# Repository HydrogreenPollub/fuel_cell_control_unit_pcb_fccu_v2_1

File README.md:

# fuel_cell_control_unit_pcb_fccu_v2_1

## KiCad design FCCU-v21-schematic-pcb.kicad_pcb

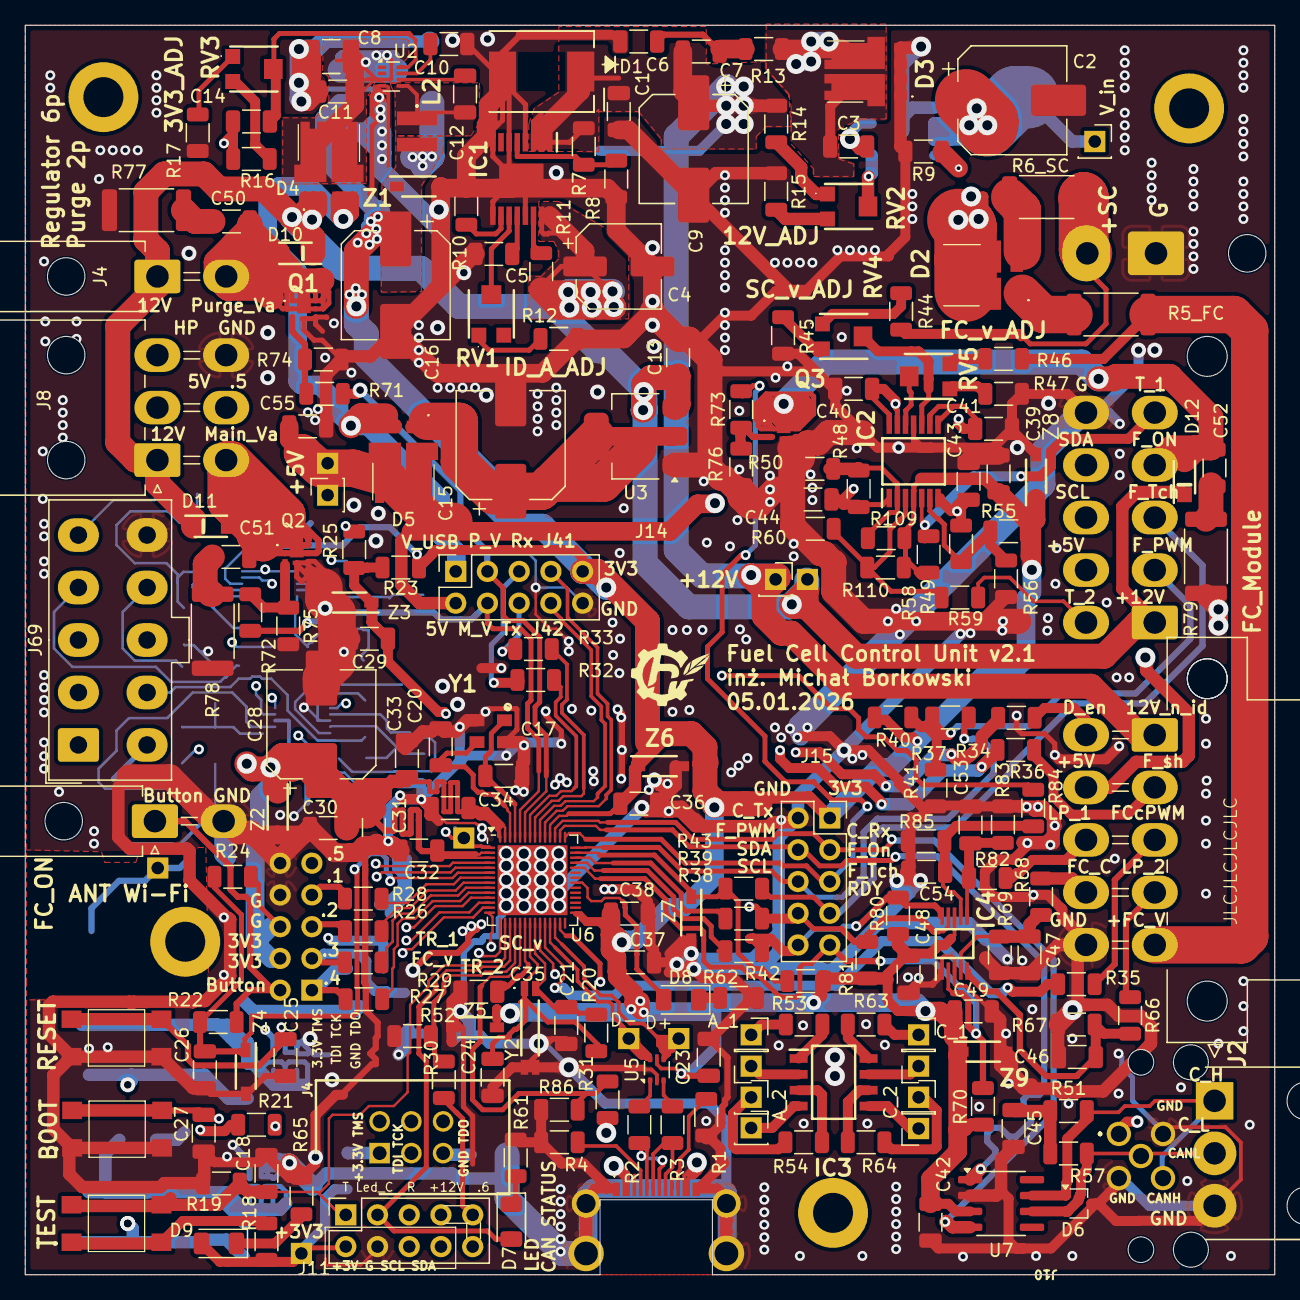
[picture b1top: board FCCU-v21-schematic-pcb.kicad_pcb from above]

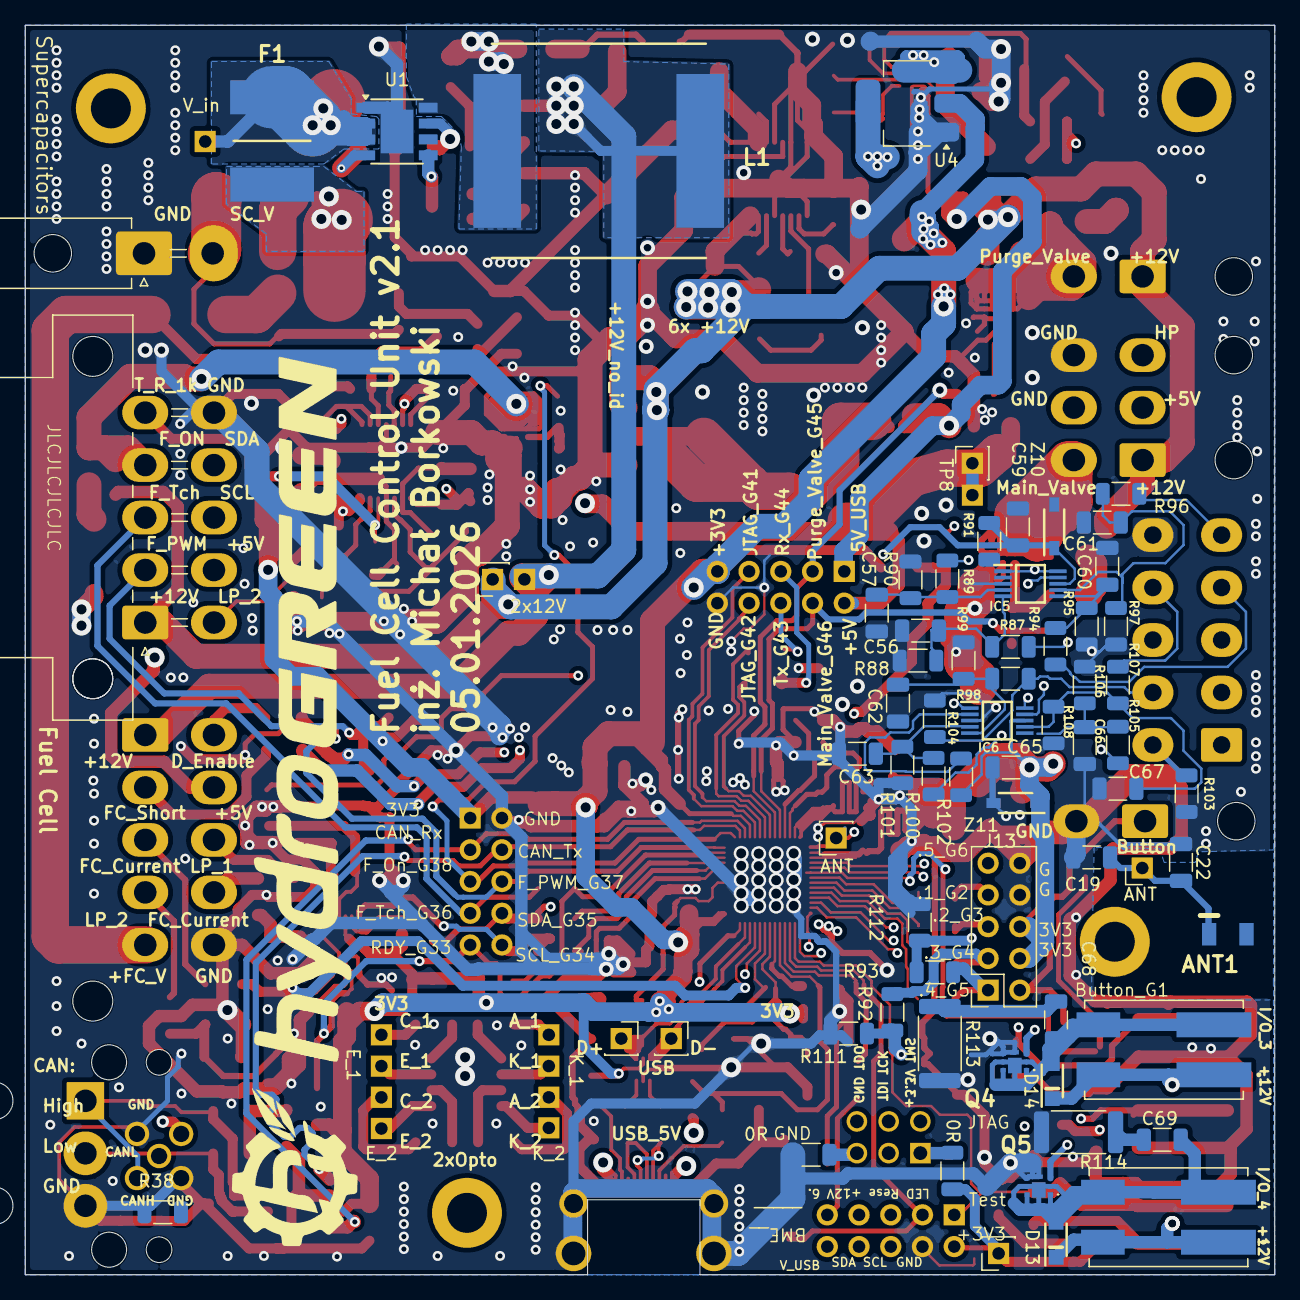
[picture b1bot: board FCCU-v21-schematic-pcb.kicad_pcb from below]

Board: 4 copper layers, 100.0 x 100.0 mm, 276 parts (68 on the bottom side), 165 nets.

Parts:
0R, 0R#2: 0; R_1206_3216Metric
2x12V: +5V; PinSocket_1x01_P2.54mm_Vertical
+3V3: +3.3V; PinSocket_1x01_P2.54mm_Vertical
+5V, +12V: +5V; PinSocket_1x01_P2.54mm_Vertical
ANT: Ant; PinSocket_1x01_P2.54mm_Vertical
ANT1: 2450AT18B100E; ANTC3216X140N
A_1: A_1; PinSocket_1x01_P2.54mm_Vertical
A_2: A_2; PinSocket_1x01_P2.54mm_Vertical
BOOT: TL3305BF100QG; TL3305BF160QG
C1, C13, C30, C33, C38, C55: 1u; C_1206_3216Metric
C2: 10u 100V; CP_Elec_8x10.5
C3: 2n2 100V; C_1206_3216Metric
C4: 47u; CP_Elec_6.3x7.7
C5: 2n7; C_1206_3216Metric
C6, C14: 47p; C_1206_3216Metric
C7: 3n3; C_1206_3216Metric
C8: 1-10u; C_1210_3225Metric_Pad1.33x2.70mm_HandSolder
C9, C15: 22u; CP_Elec_8x10.5
C10: 33n; C_1206_3216Metric
C11, C12, C18, C23, C25, C27, C31, C32, C35, C36, C37, C39, C42, C48: 100n; C_1206_3216Metric
C16: 100u; CP_Elec_8x10.5
C17, C20: 12p; C_1206_3216Metric
C19, C22: 1p2; C_1206_3216Metric
C21, C24: 20p; C_1206_3216Metric
C26, C29: 0; C_1206_3216Metric
C28: 10u; CP_Elec_8x10.5
C34: 10n; C_1206_3216Metric
C40, C41, C44, C46, C47, C53, C54: c; C_1206_3216Metric
C43, C45: 4n7; C_1206_3216Metric
C49, C59, C65: 4N7; C_1206_3216Metric
C50, C51, C52, C68, C69: 20n; C_1206_3216Metric
C56, C57, C60, C61, C66, C67: NP; C_1206_3216Metric
C62, C63: 3n; C_1206_3216Metric
C_1: C_1; PinSocket_1x01_P2.54mm_Vertical
C_2: C_2; PinSocket_1x01_P2.54mm_Vertical
D1: TPSMC30CA; TPSMCSeries_LTF
D2, D3, D4, D5: V10K100DUHM3_H; V10K100DUHM3H
D6: SP0502BAJT; SOT-323_SC-70
D7, D8, D9: LED; LED_1206_3216Metric
D10, D11, D12, D13, D14: PMEG10020; PMEG10020ELR
E_1: E_1; PinSocket_1x01_P2.54mm_Vertical
E_2: E_2; PinSocket_1x01_P2.54mm_Vertical
F1: 3A; FUSC8664X180N
I/O_3  +12V, I/O_4  +12V: 2060-453/998-404; WAGO-2060-452-998-404
IC1: LM76202QPWPRQ1; SOP65P640X120-17N
IC2: AD8544ARUZ-REEL; SOP65P640X120-14N
IC3: ILD206T; SOIC127P610X323-8N
IC4, IC5, IC6: ADS1015IDGSR; SOP50P490X110-10N
J1: Supercapacitors; Molex_Mini-Fit_Jr_5569-02A2_2x01_P4.20mm_Horizontal
J2: CAN; 39303035
J4: P_Valve; Molex_Mini-Fit_Jr_5569-02A2_2x01_P4.20mm_Horizontal
J4#2: 61200621621
J5: FC_ON; Molex_Mini-Fit_Jr_5569-02A2_2x01_P4.20mm_Horizontal
J6: FC Module; Molex_Mini-Fit_Jr_5569-10A1_2x05_P4.20mm_Horizontal
J7: FC Cooling; Molex_Mini-Fit_Jr_5569-10A1_2x05_P4.20mm_Horizontal
J8: M_Valve; Molex_Mini-Fit_Jr_5569-06A2_2x03_P4.20mm_Horizontal
J10: M12A-05PMMR-SF7003; M12A05PMMRSF7003
J11: BME; PinSocket_2x05_P2.54mm_Vertical
J13: I/O; PinSocket_2x05_P2.54mm_Vertical
J14: Top signals; PinSocket_2x05_P2.54mm_Vertical
J15: Fuel cell signals; PinSocket_2x05_P2.54mm_Vertical
J69: ADC, Freq, 4-20mA; Molex_Mini-Fit_Jr_5566-10A_2x05_P4.20mm_Vertical
K_1: K_1; PinSocket_1x01_P2.54mm_Vertical
K_2: K_2; PinSocket_1x01_P2.54mm_Vertical
L1: IHLP6767DZER470M11
L2: 4u7; SRN3015TA4R7M
P1: USB_C_Plug_USB2.0; 2169900002
Q1, Q2, Q3, Q4, Q5: PMPB10XNX; PMPB15XPAX
R1, R4: 5k1; R_1206_3216Metric
R2, R3, R72, R73: 0; R_1206_3216Metric
R5_FC, R6_SC: 0R; R_2512_6332Metric
R7: 180k; R_1206_3216Metric
R8, R87, R89, R94, R96: 12k; R_1206_3216Metric
R9, R10, R11: 100k; R_1206_3216Metric
R12: 5k6; R_1206_3216Metric
R13: 143k; R_1206_3216Metric
R14: 453k; R_1206_3216Metric
R15: 49k9; R_1206_3216Metric
R16: 47k; R_1206_3216Metric
R17, R67, R69, R83, R85, R86, R106, R108: 15k; R_1206_3216Metric
R18, R19, R21, R23, R24, R31, R40, R41, R42, R48, R49, R52, R55, R58, R66, R68, R74, R75, R76, R82, R84, R105, R107, R109, R110, R111, R112: 10k; R_1206_3216Metric
R20: 5M; R_1206_3216Metric
R22, R25, R26, R28, R30, R34, R35, R36, R43, R50, R53, R54, R56, R61, R62, R63, R64, R65: 1k; R_1206_3216Metric
R27, R29, R37: 200R; R_1206_3216Metric
R32, R33: 100R; R_1206_3216Metric
R38, R38#2, R39, R59: 0R; R_1206_3216Metric
R44, R46: 6k8; R_1206_3216Metric
R45, R47: 3k3; R_1206_3216Metric
R51, R57: 60; R_1206_3216Metric
R60: k; R_1206_3216Metric
R70, R91, R102: 2k; R_1206_3216Metric
R71: 180R; R_1206_3216Metric
R77, R78, R79, R113, R114: 100R 0,5W; R_2512_6332Metric
R80, R81: 4k7; R_1206_3216Metric
R88, R90, R95, R97: 18k; R_1206_3216Metric
R92, R93: 20; R_1206_3216Metric
R98, R100: 6k; R_1206_3216Metric
R99, R101: 130k; R_1206_3216Metric
R103, R104: 150R; R_1206_3216Metric
RESET: TL3305BF100QG; TL3305BF160QG
RV1, RV2: Pot_12V 20k; TC33X2503E
RV3: Pot_12V 5k; TC33X2503E
RV4, RV5: Pot_12V 2k; TC33X2503E
TEST: TL3305BF100QG; TL3305BF160QG
TP3: Ant; PinSocket_1x01_P2.54mm_Vertical
TP8: +5V; PinSocket_1x01_P2.54mm_Vertical
TP12: USB_D+; PinSocket_1x01_P2.54mm_Vertical
TP13: USB_D-; PinSocket_1x01_P2.54mm_Vertical
U1: LM5013DDAR; Diodes_SO-8EP
U2: TPS62933; SOT-583-8
U3: LDI1117-05H; SOT-223-3_TabPin2
U4: LDI1117-3.3H; SOT-223-3_TabPin2
U5: USBLC6-2P6; SOT-666
U6: ESP32-S3FN8; QFN-56-1EP_7x7mm_P0.4mm_EP5.6x5.6mm
U7: SN65HVD232; SOIC-8_3.9x4.9mm_P1.27mm
V_in: Vin test; PinSocket_1x01_P2.54mm_Vertical
Y1: Crystal_40MHz; KC3225K400000C1GE00
Y2: 9HT7-32.768KDZF-T; 9HT732768KDZFT
Z1, Z2, Z3, Z4, Z5, Z6, Z7, Z8, Z9, Z10, Z11: MMSZ3V3T1G; SOD3716X135N

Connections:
+3.3V: 0R.2, +3V3.1, C14.1, C16.1, C23.1, C28.1, C30.1, C31.1, C32.1, C33.1, C34.1, C35.1, C36.1, C37.1, C38.1, C39.1, C42.1, C48.1, C49.1, C59.1, C65.1, D9.2 (A), IC2.4 (V+), IC4.8 (VDD), IC5.8 (VDD), IC6.1 (ADDR), IC6.8 (VDD), J11.6, J13.7, J13.8, J14.5, J15.1, L2.2, R16.1, R18.2, R21.2, R23.2, R24.2, R40.2, R42.2, R55.1, R58.1, R70.1, R80.1, R81.1, R91.1, R102.1, R109.2, R110.1, U4.2 (VO), U5.5 (VBUS), U6.2 (VDD3P3), U6.3 (VDD3P3), U6.20 (VDD3P3_RTC), U6.29 (VDD_SPI), U6.46 (VDD3P3_CPU), U6.55 (VDDA), U6.56 (VDDA), U7.3 (VCC), Z1.1 (K), Z2.1 (K), Z5.1 (K), Z6.1 (K), Z8.1 (K), Z9.1 (K), Z10.1 (K), Z11.1 (K)
+3V3: 0R.1, J4#2.1
+5V: +5V.1, C55.1, D5.5, D5.6, D5.7, D5.8, J6.7, J7.7, J8.2, J14.6, TP8.1 (1_1)
+12V: 2x12V.1, +12V.1, C4.1, C13.1, D4.1, D4.2, D10.1 (K), D11.1 (K), D12.1 (K), D13.1 (K), D14.1 (K), IC1.15 (OUT_1), IC1.16 (OUT_2), J4.1, J7.1, J8.1, J11.4, J69.1, R11.1, U3.3 (VI)
/12V_no_id: C1.1, C7.2, C9.1, D1.2 (A), IC1.1 (IN_1), IC1.2 (IN_2), IC1.3 (UVLO), J6.1, J10.1, L1.2, R7.1, R14.2
/IO2/ADC2_0: J69.2, R89.1
/IO2/ADC2_1: J69.3, R87.1
/IO2/ADC2_2: J69.4, R94.1
/IO2/ADC2_3: J69.5, R96.1
/IO2/ADC3_0: J69.6, R100.1, R103.1
/IO2/ADC3_1: J69.7, R98.1, R104.1
/IO2/ADC3_2: J69.8, R105.1
/IO2/ADC3_3: J69.9, R107.1
/IO2/I/O_3: C68.1, D14.2 (A), Q4.1 (D)
/IO2/I/O_4: C69.1, D13.2 (A), Q5.1 (D)
/IO2/SCL_MCU: IC5.1 (ADDR), IC5.10 (SCL), IC6.10 (SCL)
/IO2/SDA_MCU: IC5.9 (SDA), IC6.9 (SDA)
/IO/CANH: D6.1 (K), J2.1, J10.3, R51.2, U7.7 (CANH)
/IO/CANL: D6.2 (K), J2.2, J10.5, R57.2, U7.6 (CANL)
/IO/CAN_RX_G39: J4#2.TDO, U7.4 (R)
/IO/FAN_ON: C52.1, D12.2 (A), J7.4, Q3.1 (D)
/IO/FAN_ON_MCU: J15.3, R73.2
/IO/FAN_TACHO: J7.3, J15.4
/IO/FC_C: J6.9, R68.1
/IO/FC_V: J6.5, R5_FC.1, R46.2
/IO/FC_VOLTAGE_MCU: C40.2, IC2.13 (-IN_D), IC2.14 (OUT_D)
/IO/HP: J8.3, R84.1
/IO/LED_CAN_STATUS: D7.2 (A), J11.2
/IO/LP_1: J6.8, R82.1
/IO/LP_2: J6.4, R66.1
/IO/MAIN_VALVE_MCU: J14.7, R72.2
/IO/Main_Valve: C51.1, D11.2 (A), J8.4, Q2.1 (D)
/IO/PURGE_VALVE: C50.1, D10.2 (A), J4.2, Q1.1 (D)
/IO/PURGE_VALVE_MCU: J14.2, R71.2
/IO/RDY_MCU: IC4.2 (ALERT/RDY), J15.5, R70.2
/IO/SCL_FC: IC4.10 (SCL), J7.8, J15.10, R80.2
/IO/SC_V: J1.2, R6_SC.1, R44.2
/IO/SC_VOLTAGE_MCU: C41.2, IC2.8 (OUT_C), IC2.9 (-IN_C)
/IO/SDA_FC: IC4.9 (SDA), J7.9, J15.9, R81.2
/IO/T1_G10: C43.1, IC2.7 (OUT_B), R49.2
/IO/T2_G7: C44.2, IC2.1 (OUT_A), R48.1
/IO/TEMP_SENSOR_1: IC2.5 (+IN_B), J7.5, R58.2
/IO/TEMP_SENSOR_2: IC2.3 (+IN_A), J7.6, R59.1
/MCU/Antena: ANT.1, C22.1, TP3.1 (1_1), U6.1 (LNA_IN/RF)
/MCU/BOOT: BOOT.3 (K), BOOT.4 (A), C27.1, U6.5 (GPIO0/BOOT)
/MCU/BUTTON_MCU_G36: J5.1, J13.6
/MCU/FAN_IN_PWM_G37: R37.1, R40.1, R41.1
/MCU/FAN_PWM: J15.8, R37.2, U6.42 (GPIO37)
/MCU/FC_CURRENT_PWM_G18: J6.3, R35.1
/MCU/I/O_1_G2: J13.4, R28.2
/MCU/I/O_2_G3: J13.3, R26.2
/MCU/I/O_3_G4: J13.2, R29.2
/MCU/I/O_4_G5: J13.1, R27.2
/MCU/I/O_5_G6: J13.5, R25.1
/MCU/JTAG_TCK_G41: J4#2.4, J14.4, U6.47 (MTDI/JTAG/GPIO41)
/MCU/JTAG_TDI_G40: J4#2.3, U6.45 (MTDO/JTAG/GPIO40)
/MCU/JTAG_TMS_G42: J4#2.2, J14.9, U6.48 (MTMS/JTAG/GPIO42)
/MCU/MCU_TEST_G11: C18.1, J11.1, R19.2, TEST.3 (K), TEST.4 (A), U6.16 (GPIO11/ADC2_CH0)
/MCU/RESET: C25.1, J11.3, R21.1, RESET.3 (K), RESET.4 (A), U6.4 (CHIP_PU/RESET)
/MCU/Rx_G44: J14.3, R32.2
/MCU/Tx_G43: J14.8, R33.1
/MCU/USB_D+: R3.2, TP12.1 (1_1), U5.3 (I/O2), U5.4 (I/O2), U6.26 (GPIO20/USB_D+/ADC2_CH9)
/MCU/USB_D-: R2.2, TP13.1 (1_1), U5.1 (I/O1), U5.6 (I/O1), U6.25 (GPIO19/USB_D-/ADC2_CH8)
/MCU/XTAL_N: C17.1, U6.53 (XTAL_N), Y1.1
/MCU/XTAL_N_32: C21.1, R20.1, U6.22 (GPIO16/ADC2_CH5/XTAL_32K_N), Y2.4 (X2)
/MCU/XTAL_P: C20.1, U6.54 (XTAL_P), Y1.3
/MCU/XTAL_P_32: C24.1, R20.2, U6.21 (GPIO15/ADC2_CH4/XTAL_32K_P), Y2.1 (X1)
/Power/3V3_reg_in: C8.1, C11.1, D4.5, D4.6, D4.7, D4.8, U2.3 (VIN), U4.3 (VI)
/Power/FB_12: RV2.2, U1.5 (FB)
/VBUS: D4.3, D4.4, D5.3, D5.4, J11.10, J14.1, P1.A4 (VBUS), P1.A9 (VBUS), P1.B4 (VBUS), P1.B9 (VBUS), R31.2
GND: 0R#2.1, BOOT.1, BOOT.2, C1.2, C2.2, C4.2, C5.2, C6.1, C8.2, C9.2, C10.2, C11.2, C13.2, C15.2, C16.2, C17.2, C18.2, C19.1, C20.2, C21.2, C22.2, C23.2, C24.2, C25.2, C26.2, C27.2, C28.2, C29.2, C30.2, C31.2, C32.2, C33.2, C34.2, C35.2, C36.2, C37.2, C38.2, C39.2, C40.1, C41.1, C42.2, C43.2, C44.1, C45.2, C46.2, C47.2, C48.2, C49.2, C53.2, C54.2, C55.2, C56.2, C57.2, C59.2, C60.2, C61.2, C62.2, C63.2, C65.2, C66.2, C67.2, D1.1 (K), D3.1, D3.2, D3.3, D3.4, D6.3 (A), IC1.4 (NC_1), IC1.6 (MODE), IC1.8 (RTN), IC1.9 (GND), IC1.13 (NC_2), IC1.17 (EP), IC2.11 (GND), IC4.1 (ADDR), IC4.3 (GND), IC5.3 (GND), IC6.3 (GND), J1.1, J2.3, J5.2, J6.10, J7.10, J8.6, J10.2, J10.4, J11.7, J13.9, J13.10, J14.10, J15.6, J69.10, P1.A1 (GND), P1.A12 (GND), P1.B1 (GND), P1.B12 (GND), Q1.3 (S), Q2.3 (S), Q3.3 (S), Q4.3 (S), Q5.3 (S), R1.2, R4.2, R8.2, R9.2, R10.2, R12.2, R15.1, R17.2, R19.1, R41.2, R45.1, R47.1, R50.2, R52.1, R56.2, R60.2, R61.2, R62.2, R65.2, R67.2, R69.2, R74.2, R75.2, R76.2, R77.2, R78.2, R79.2, R83.2, R85.2, R86.1, R88.2, R90.2, R95.2, R97.2, R99.2, R101.2, R103.2, R104.2, R106.2, R108.2, R111.2, R112.2, R113.2, R114.2, RESET.1, RESET.2, U1.1 (GND), U1.9 (EP), U2.4 (GND), U3.1 (GND), U4.1 (GND), U5.2 (GND), U6.57 (GND), U7.2 (GND), Y1.2, Y1.4, Y2.2 (GND_1), Y2.3 (GND_2), Z1.2 (A), Z2.2 (A), Z3.2 (A), Z4.2 (A), Z5.2 (A), Z6.2 (A), Z7.2 (A), Z8.2 (A), Z9.2 (A), Z10.2 (A), Z11.2 (A)
unnamed: ANT1.1 (FEED_1), C19.2
unnamed: A_1.1 (1_1), R53.1
unnamed: A_2.1 (1_1), R54.1
unnamed: C6.2, C7.1, R13.2
unnamed: C45.1, R51.1, R57.1
unnamed: C50.2, R77.1
unnamed: C51.2, R78.1
unnamed: C52.2, R79.1
unnamed: C68.2, R113.1
unnamed: C69.2, R114.1
unnamed: C_1.1 (1_1), R63.2
unnamed: C_2.1 (1_1), R64.2
unnamed: D2.1, D2.2, R5_FC.2
unnamed: D2.3, D2.4, R6_SC.2
unnamed: D2.5, D2.6, D2.7, D2.8, F1.1
unnamed: D7.1 (K), R61.1
unnamed: D8.1 (K), R62.1
unnamed: D9.1 (K), R65.1
unnamed: C5.1, IC1.12 (DVDT)
unnamed: IC1.11 (ILIM), RV1.2
unnamed: IC1.10 (IMON), R10.1
unnamed: IC1.5 (OVP), R7.2, R8.1
unnamed: IC1.14 (~FLT), R11.2
unnamed: R59.2, R60.1, R110.2
unnamed: IC2.10 (+IN_C), RV4.2
unnamed: IC2.12 (+IN_D), RV5.2
unnamed: IC2.2 (-IN_A), R48.2, R50.1, R109.1
unnamed: IC2.6 (-IN_B), R49.1, R55.2, R56.1
unnamed: IC3.1 (A_1), R53.2
unnamed: IC3.3 (A_2), R54.2
unnamed: IC3.8 (C_1), R63.1
unnamed: IC3.6 (C_2), R64.1
unnamed: E_1.1 (1_1), IC3.7 (E_1)
unnamed: E_2.1 (1_1), IC3.5 (E_2)
unnamed: IC3.2 (K_1), K_1.1 (1_1)
unnamed: IC3.4 (K_2), K_2.1 (1_1)
unnamed: C47.1, IC4.4 (AIN0), R68.2, R69.1
unnamed: C46.1, IC4.5 (AIN1), R66.2, R67.1
unnamed: C53.1, IC4.6 (AIN2), R82.2, R83.1
unnamed: C54.1, IC4.7 (AIN3), R84.2, R85.1
unnamed: C57.1, IC5.4 (AIN0), R89.2, R90.1
unnamed: C56.1, IC5.5 (AIN1), R87.2, R88.1
unnamed: C60.1, IC5.6 (AIN2), R94.2, R95.1
unnamed: C61.1, IC5.7 (AIN3), R96.2, R97.1
unnamed: IC5.2 (ALERT/RDY), R91.2
unnamed: C63.1, IC6.4 (AIN0), R100.2, R101.1
unnamed: C62.1, IC6.5 (AIN1), R98.2, R99.1
unnamed: C66.1, IC6.6 (AIN2), R105.2, R106.1
unnamed: C67.1, IC6.7 (AIN3), R107.2, R108.1
unnamed: IC6.2 (ALERT/RDY), R102.2
unnamed: P1.A5 (CC), R4.1
unnamed: P1.A6 (D+), P1.B6 (D+), R3.1
unnamed: P1.A7 (D-), P1.B7 (D-), R2.1
unnamed: P1.B5 (VCONN), R1.1
unnamed: Q1.2 (G), Q4.2 (G), Q5.2 (G), R71.1, R74.1
unnamed: Q2.2 (G), R72.1, R75.1
unnamed: Q3.2 (G), R73.1, R76.1
unnamed: R92.1, R111.1
unnamed: R93.1, R112.1
unnamed: R12.1, RV1.1
unnamed: R14.1, RV2.3
unnamed: R15.2, RV2.1
unnamed: R16.2, RV3.3
unnamed: R17.1, RV3.1
unnamed: R18.1, TEST.1, TEST.2
unnamed: R44.1, RV4.1
unnamed: R45.2, RV4.3
unnamed: R46.1, RV5.1
unnamed: R47.2, RV5.3
unnamed: C3.2, U1.7 (BST)
unnamed: C2.1, F1.2, U1.2 (VIN), U1.3 (EN_UVLO), V_in.1
unnamed: R9.1, U1.4 (RON)
unnamed: C3.1, D3.5, D3.6, D3.7, D3.8, L1.1, R13.1, U1.8 (SW)
unnamed: C12.1, U2.6 (BST)
unnamed: C14.2, RV3.2, U2.8 (FB)
unnamed: C10.1, U2.7 (SS)
unnamed: C12.2, L2.1, U2.5 (SW)
unnamed: C15.1, D5.1, D5.2, U3.2 (VO)
unnamed: C26.1, R22.1, R24.1, U6.6 (GPIO1/ADC1_CH0), Z4.1 (K)
unnamed: R28.1, U6.7 (GPIO2/ADC1_CH1)
unnamed: R26.1, U6.8 (GPIO3/ADC1_CH2)
unnamed: R29.1, U6.9 (GPIO4/ADC1_CH3)
unnamed: R27.1, U6.10 (GPIO5/ADC1_CH4)
unnamed: C29.1, R23.1, R25.2, U6.11 (GPIO6/ADC1_CH5), Z3.1 (K)
unnamed: R30.1, R52.2, U6.18 (GPIO13/ADC2_CH2)
unnamed: R31.1, R86.2, U6.19 (GPIO14/ADC2_CH3)
unnamed: R36.2, U6.23 (GPIO17/ADC2_CH6)
unnamed: R35.2, U6.24 (GPIO18/ADC2_CH7)
unnamed: R34.2, U6.27 (GPIO21)
unnamed: R38.1, U6.39 (GPIO34)
unnamed: R39.1, U6.40 (GPIO35)
unnamed: R42.1, R43.1, U6.41 (GPIO36), Z7.1 (K)
unnamed: R32.1, U6.50 (U0RXD/PROG/GPIO44)
unnamed: R33.2, U6.49 (U0TXD/PROG/GPIO43)
